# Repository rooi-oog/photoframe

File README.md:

# Digital Photoframe

This is FPGA based digital photoframe project. It capable read jpeg files from SD card and display them to TFT LCD.

### This project utilizes:
* Cyclone IV EP4CE15E22C8 as a heart of whole system
* LatticeMico32 soft-CPU to decode jpeg
* 256Mb SDRAM SDR16 as a framebuffer
* EPCS16 both for configure FPGA and store photoframe's firmware
* Hannstar HDS101PWW2 LVDS display
* FatFs library by [Elm ChaN](http://elm-chan.org/fsw/ff/00index_e.html) 
* TJpegd library by [Elm ChaN](http://elm-chan.org/fsw/tjpgd/00index.html)
	
Most of the code both software and hardware borrowed from [Milkymist(tm)](https://github.com/m-labs/milkymist) project. 
SDRAM controller was borrowed from [Stefan Kristiansson](https://github.com/skristiansson/wb_sdram_ctrl)
SDRAM controller was slightly modified with purpose to give priority to the first master (framebuffer) in case of rivalry.

### Limitations:
For this project I'm using 10.1" LCD with 1280x800 screen resolutuion. In order to display various jpeg images 
user should downscale that images to LCD resolutuion. 
Furthermore Tjpegd library only capable to decode baseline and 4:2:0 subsampling jpegs. 
For this purpose I wrote small script which is located at *software/tools/conv.sh*. 
This script uses ImageMagick for converting all images in given directory to:
- baseline
- 4:2:0 subsampling
- 1280x800 or 800x1280 depending of image orientation

### How to reproduce:
If you're using **DE0-Nano** development board you'll need **Quartus** software. **Web Edition** will be enough.
Then you should upload *pframe.sof* file which is located at *board/de0-nano/syn/output_files* 
or you can upload firmware to the EPCS16 with *epcs16.cdf*. 
Futher you should use *serial_upload* program located at *software/tools* 
to write photoframe's firmare through uart to the device either directly in SDRAM or in EPCS16.

In case if you're using other devices/environments you have to make an effort to force this project work all by yourself. :)

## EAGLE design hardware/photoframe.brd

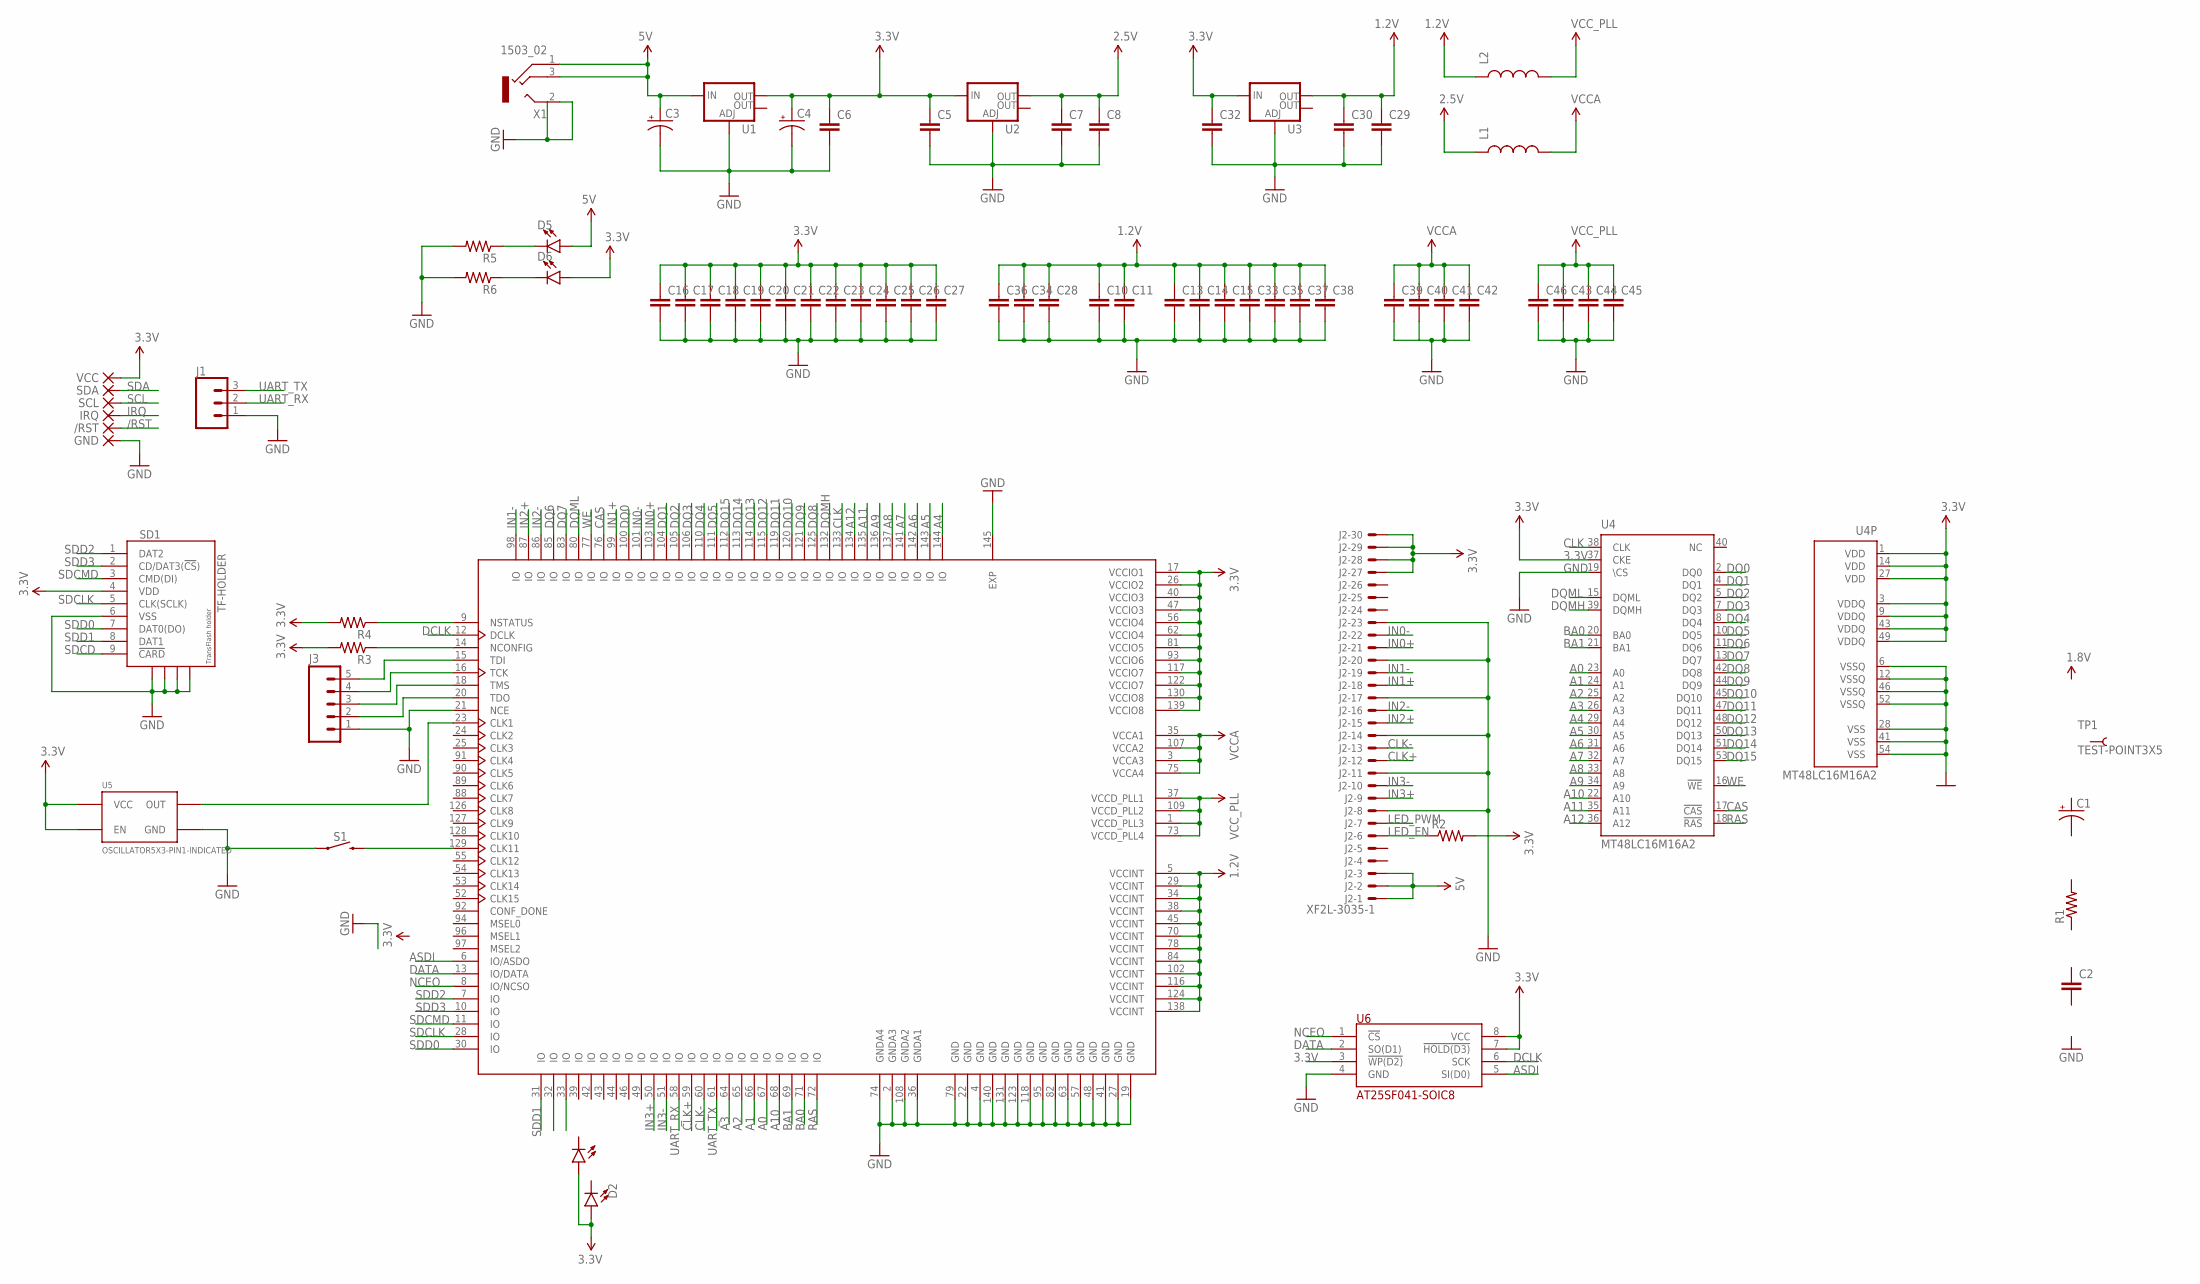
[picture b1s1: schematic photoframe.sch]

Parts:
/RST: PAD-SMD15R; SMD15R
C1, C3, C4: CAP_POL1206-KIT; EIA3216-KIT
C2, C8: CAP0603-CAP; 0603-CAP
C5, C7, C30, C32: CAP1206; 1206
C6, C29, C45: CAP0805; 0805
C10, C11, C13, C14, C15, C16, C17, C18, C19, C20, C21, C22, C23, C24, C25, C26, C27, C28, C33, C34, C35, C36, C37, C38, C39, C40, C41, C42, C43, C44, C46: CAP0402-CAP; 0402-CAP
D1, D2: LED0603; LED-0603
D5, D6: LED1206; LED-1206
GND: PAD-SMD14R; SMD14R
IRQ: PAD-SMD15R; SMD15R
J1: CONN_03LONGPADS; 1X03_LONGPADS
J2: XF2L-3035-1
J3: M05PTH_LONGPADS; 1X05_LONGPADS
L1, L2: INDUCTOR0805-IND; 0805
R1, R5, R6: RESISTOR0603-RES; 0603-RES
R2, R3, R4: RESISTOR0402-RES; 0402-RES
S1: MOMENTARY-SWITCH-SPST-SMD-5.2-TALL-REDUNDANT; TACTILE_SWITCH_SMD_5.2MM
SCL: PAD-SMD15R; SMD15R
SD1: TF-HOLDER; TF-PULL
SDA: PAD-SMD15R; SMD15R
TP1: TEST-POINT3X5; PAD.03X.05
U0: EP4CE15E22; QFP50P2200X2200X165-145N
U1, U2, U3: V_REG_LM1117SOT223; SOT223
U4: MT48LC16M16A2; TSOP54-400
U5: OSCILLATOR5X3-PIN1-INDICATED; CRYSTAL-OSC-SMD-5X3
U6: AT25SF041-SOIC8; SO08
VCC: PAD-SMD15R; SMD15R
X1: 1503_02

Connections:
1.0V: C10.1, C11.1, C13.1, C14.1, C15.1, C28.1, C29.1, C30.1, C33.1, C34.1, C35.1, C36.1, C37.1, C38.1, L2.1, U0.5 (VCCINT), U0.29 (VCCINT), U0.34 (VCCINT), U0.38 (VCCINT), U0.45 (VCCINT), U0.70 (VCCINT), U0.78 (VCCINT), U0.84 (VCCINT), U0.102 (VCCINT), U0.116 (VCCINT), U0.124 (VCCINT), U0.138 (VCCINT), U3.2 (OUT)
2.5V: C7.1, C8.1, L1.1, U2.2 (OUT)
3.3V: C4.A (+), C5.1, C6.1, C16.1, C17.1, C18.1, C19.1, C20.1, C21.1, C22.1, C23.1, C24.1, C25.1, C26.1, C27.1, C32.1, D1.A, D2.A, D6.A, J2.27 (MS), J2.28 (MS), J2.29 (MS), J2.30 (MS), R2.2, R3.2, R4.2, SD1.4 (VDD), U0.17 (VCCIO1), U0.26 (VCCIO2), U0.40 (VCCIO3), U0.47 (VCCIO3), U0.56 (VCCIO4), U0.62 (VCCIO4), U0.81 (VCCIO5), U0.93 (VCCIO6), U0.117 (VCCIO7), U0.122 (VCCIO7), U0.130 (VCCIO8), U0.139 (VCCIO8), U1.2 (OUT), U2.3 (IN), U3.3 (IN), U4.1 (VDD), U4.3 (VDDQ), U4.9 (VDDQ), U4.14 (VDD), U4.27 (VDD), U4.37 (CKE), U4.43 (VDDQ), U4.49 (VDDQ), U5.1 (EN), U5.4 (VCC), U6.3 (!WP(D2)), U6.7 (!HOLD(D3)), U6.8 (VCC), VCC.PAD
5V: C3.A (+), D5.A, J2.1 (MSV), J2.2 (MS), J2.3 (MS), U1.3 (IN), X1.1, X1.3
/RST: /RST.PAD
A0: U0.67 (IO), U4.23 (A0)
A1: U0.66 (IO), U4.24 (A1)
A2: U0.65 (IO), U4.25 (A2)
A3: U0.64 (IO), U4.26 (A3)
A4: U0.144 (IO), U4.29 (A4)
A5: U0.143 (IO), U4.30 (A5)
A6: U0.142 (IO), U4.31 (A6)
A7: U0.141 (IO), U4.32 (A7)
A8: U0.137 (IO), U4.33 (A8)
A9: U0.136 (IO), U4.34 (A9)
A10: U0.68 (IO), U4.22 (A10)
A11: U0.135 (IO), U4.35 (A11)
A12: U0.134 (IO), U4.36 (A12)
ASDI: U0.6 (IO/ASDO), U6.5 (SI(D0))
BA0: U0.71 (IO), U4.20 (BA0)
BA1: U0.69 (IO), U4.21 (BA1)
CAS: U0.76 (IO), U4.17 (!CAS)
CLK: U0.133 (IO), U4.38 (CLK)
CLK+: J2.12 (MS), U0.59 (IO)
CLK-: J2.13 (MS), U0.60 (IO)
DATA: U0.13 (IO/DATA), U6.2 (SO(D1))
DCLK: U0.12 (DCLK), U6.6 (SCK)
DQ0: U0.100 (IO), U4.2 (DQ0)
DQ1: U0.104 (IO), U4.4 (DQ1)
DQ2: U0.105 (IO), U4.5 (DQ2)
DQ3: U0.106 (IO), U4.7 (DQ3)
DQ4: U0.110 (IO), U4.8 (DQ4)
DQ5: U0.111 (IO), U4.10 (DQ5)
DQ6: U0.85 (IO), U4.11 (DQ6)
DQ7: U0.83 (IO), U4.13 (DQ7)
DQ8: U0.125 (IO), U4.42 (DQ8)
DQ9: U0.121 (IO), U4.44 (DQ9)
DQ10: U0.120 (IO), U4.45 (DQ10)
DQ11: U0.119 (IO), U4.47 (DQ11)
DQ12: U0.115 (IO), U4.48 (DQ12)
DQ13: U0.114 (IO), U4.50 (DQ13)
DQ14: U0.113 (IO), U4.51 (DQ14)
DQ15: U0.112 (IO), U4.53 (DQ15)
DQMH: U0.132 (IO), U4.39 (DQMH)
DQML: U0.80 (IO), U4.15 (DQML)
GND: C3.C (-), C4.C (-), C5.2, C6.2, C7.2, C8.2, C10.2, C11.2, C13.2, C14.2, C15.2, C16.2, C17.2, C18.2, C19.2, C20.2, C21.2, C22.2, C23.2, C24.2, C25.2, C26.2, C27.2, C28.2, C29.2, C30.2, C32.2, C33.2, C34.2, C35.2, C36.2, C37.2, C38.2, C39.2, C40.2, C41.2, C42.2, C43.2, C44.2, C45.2, C46.2, GND.PAD, J1.1, J2.8 (MS), J2.11 (MS), J2.14 (MS), J2.17 (MS), J2.20 (MS), J2.23 (MS), J3.1, R5.2, R6.2, S1.1, S1.2 (1), SD1.6 (VSS), SD1.S1, SD1.S2, SD1.S3, SD1.S4, U0.2 (GNDA3), U0.4 (GND), U0.19 (GND), U0.21 (NCE), U0.22 (GND), U0.27 (GND), U0.36 (GNDA1), U0.41 (GND), U0.48 (GND), U0.57 (GND), U0.63 (GND), U0.74 (GNDA4), U0.79 (GND), U0.82 (GND), U0.95 (GND), U0.108 (GNDA2), U0.118 (GND), U0.123 (GND), U0.131 (GND), U0.140 (GND), U0.145 (EXP), U1.1 (ADJ), U2.1 (ADJ), U3.1 (ADJ), U4.6 (VSSQ), U4.12 (VSSQ), U4.19 (\CS), U4.28 (VSS), U4.41 (VSS), U4.46 (VSSQ), U4.52 (VSSQ), U4.54 (VSS), U5.2 (GND), U6.4 (GND), X1.2, X1.2@2 (2)
IN0+: J2.21 (MS), U0.103 (IO)
IN0-: J2.22 (MS), U0.101 (IO)
IN1+: J2.18 (MS), U0.99 (IO)
IN1-: J2.19 (MS), U0.98 (IO)
IN2+: J2.15 (MS), U0.87 (IO)
IN2-: J2.16 (MS), U0.86 (IO)
IN3+: J2.9 (MS), U0.50 (IO)
IN3-: J2.10 (MS), U0.51 (IO)
IRQ: IRQ.PAD
LED_EN: J2.6 (MS), R2.1
LED_PWM: J2.7 (MS)
unnamed: R4.1, U0.9 (NSTATUS)
unnamed: R3.1, U0.14 (NCONFIG)
unnamed: J3.2, U0.20 (TDO)
unnamed: J3.3, U0.18 (TMS)
unnamed: J3.4, U0.16 (TCK)
unnamed: U0.23 (CLK1), U5.3 (OUT)
unnamed: J3.5, U0.15 (TDI)
unnamed: D5.C, R5.1
unnamed: D6.C, R6.1
unnamed: S1.3 (2), S1.4 (2), U0.129 (CLK11)
NCEO: U0.8 (IO/NCSO), U6.1 (!CS)
RAS: U0.72 (IO), U4.18 (!RAS)
SCL: SCL.PAD
SDA: SDA.PAD
SDCD: SD1.9 (!CARD)
SDCLK: SD1.5 (CLK(SCLK)), U0.28 (IO)
SDCMD: SD1.3 (CMD(DI)), U0.11 (IO)
SDD0: SD1.7 (DAT0(DO)), U0.30 (IO)
SDD1: SD1.8 (DAT1), U0.31 (IO)
SDD2: SD1.1 (DAT2), U0.7 (IO)
SDD3: SD1.2 (CD/DAT3(!CS!)), U0.10 (IO)
UART_RX: J1.2, U0.58 (IO)
UART_TX: J1.3, U0.61 (IO)
VCCA: C39.1, C40.1, C41.1, C42.1, L1.2, U0.3 (VCCA3), U0.35 (VCCA1), U0.75 (VCCA4), U0.107 (VCCA2)
VCC_PLL: C43.1, C44.1, C45.1, C46.1, L2.2, U0.1 (VCCD_PLL3), U0.37 (VCCD_PLL1), U0.73 (VCCD_PLL4), U0.109 (VCCD_PLL2)
WE: U0.77 (IO), U4.16 (!WE)

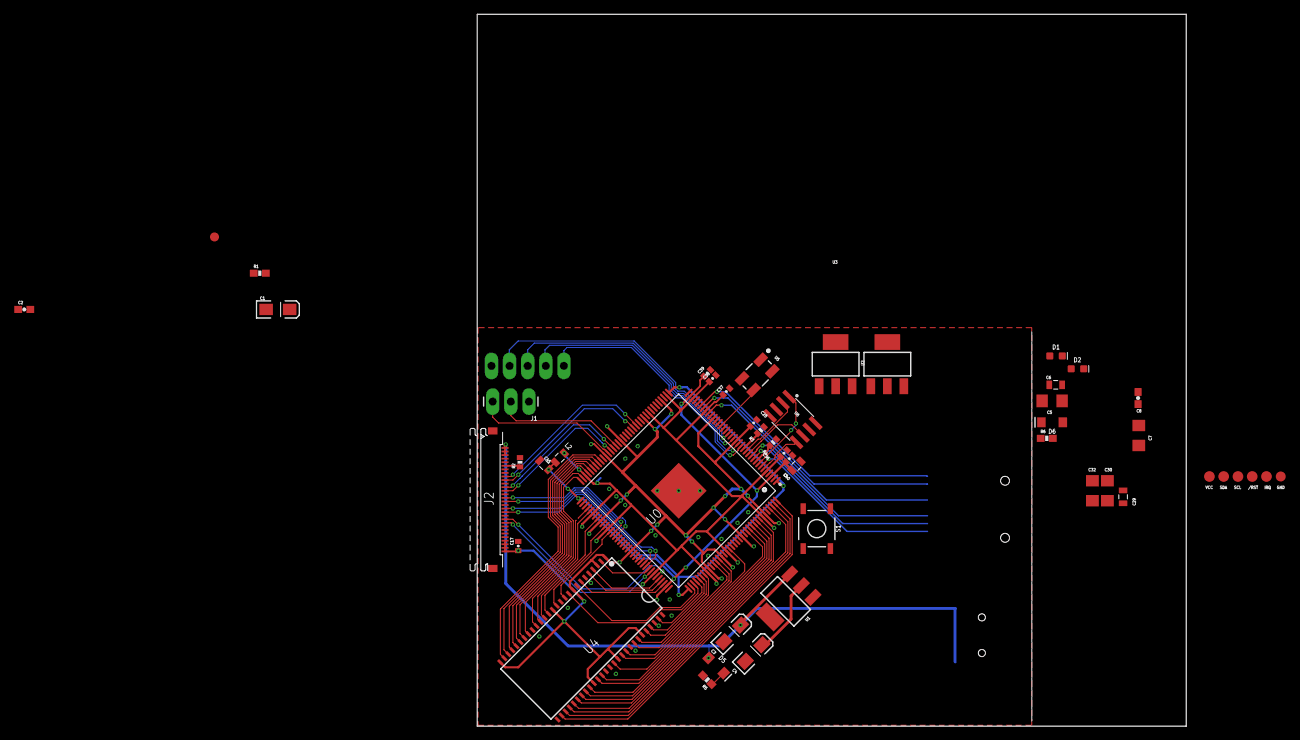
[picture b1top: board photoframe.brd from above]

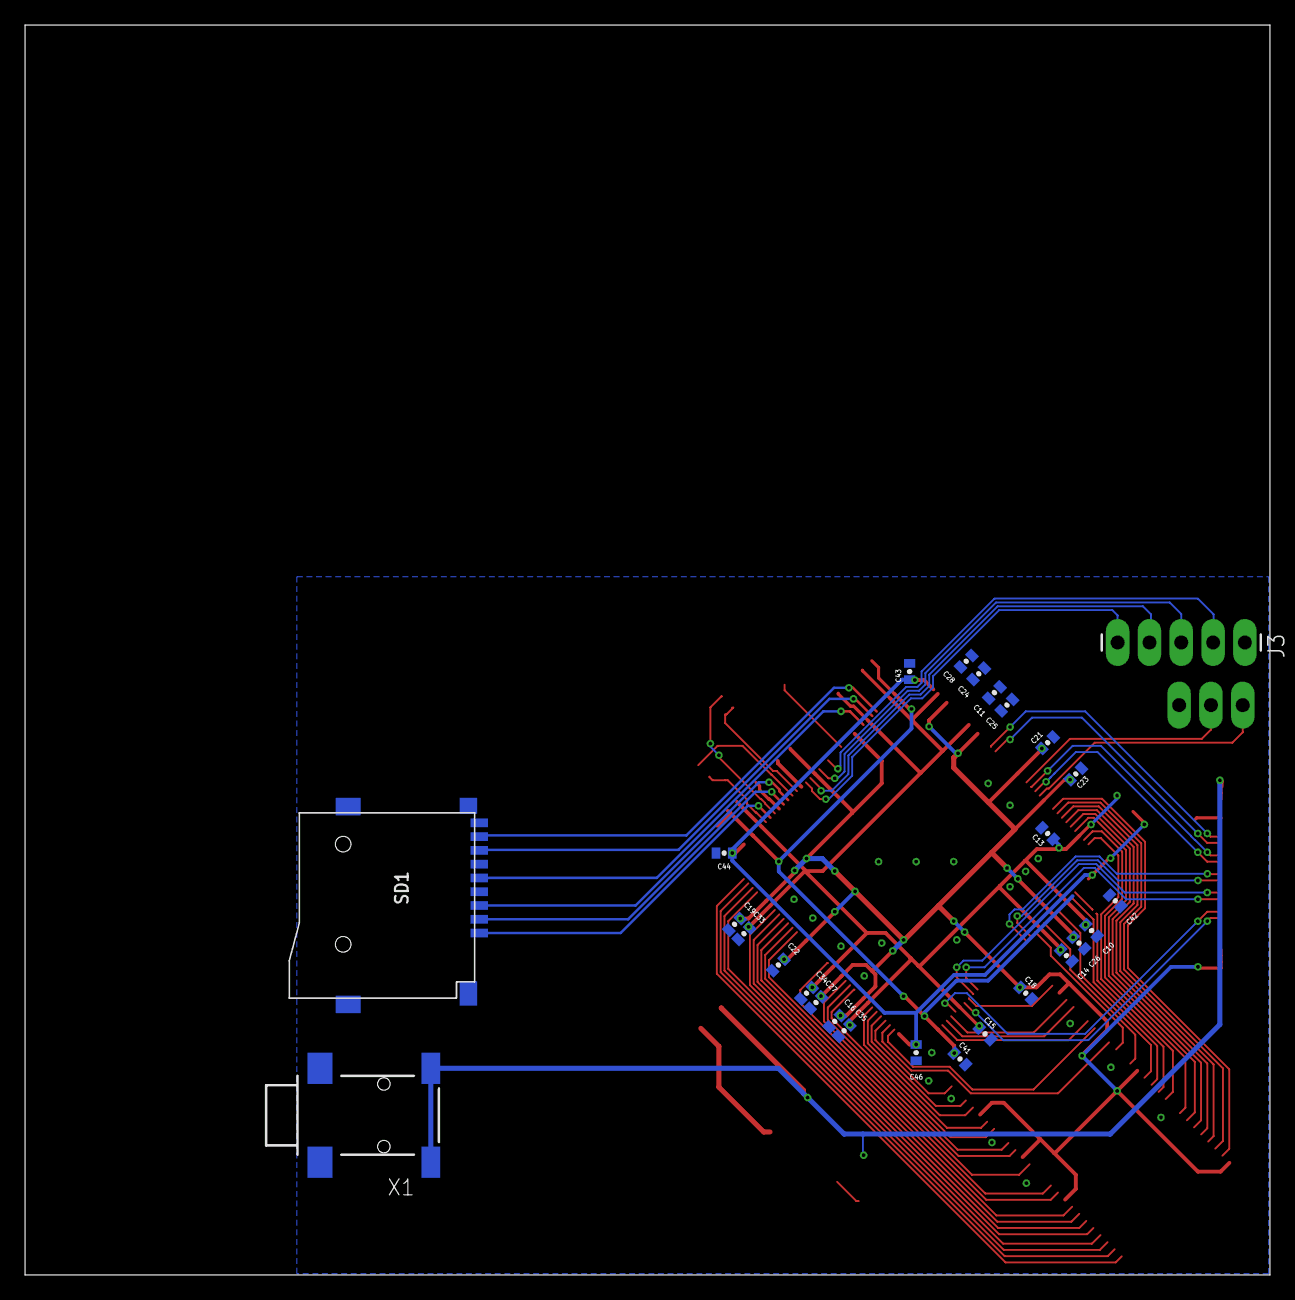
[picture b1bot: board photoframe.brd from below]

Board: 2 copper layers, 99.4 x 99.8 mm, 75 parts (27 on the bottom side), 77 nets.

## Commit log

2018-11-30 intial commit
2018-11-30 edit readme
2018-11-30 add debug defines
2018-11-30 add debug
2018-12-05 add new board
2020-01-08 some cleanup
2020-01-08 cleanup
2020-01-08 add cores
2020-01-09 add cpu

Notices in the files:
parts and their libraries:
SparkFun-Passives: Licensing: Creative Commons ShareAlike 4.0 International - https://creativecommons.org/licenses/by-sa/4.0
dpads: Copyright (C) 2004, Bob Starr (bobstarr@mindspring.com)
